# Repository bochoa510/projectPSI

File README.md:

# projectPSI : Automatic Tire Inflator prototype 

# Index

* CAD
  - housing design using OnShapeCAD
    
*  Code
   - source code used to program microcontroller
 
* Parts
    - detailed list of components used and links 
    
* Previous versions
  - previous versions, keeping for project history
    
* Resources
   - parts resources  
     
* Schematics
   - KiCAD schematic files and board design

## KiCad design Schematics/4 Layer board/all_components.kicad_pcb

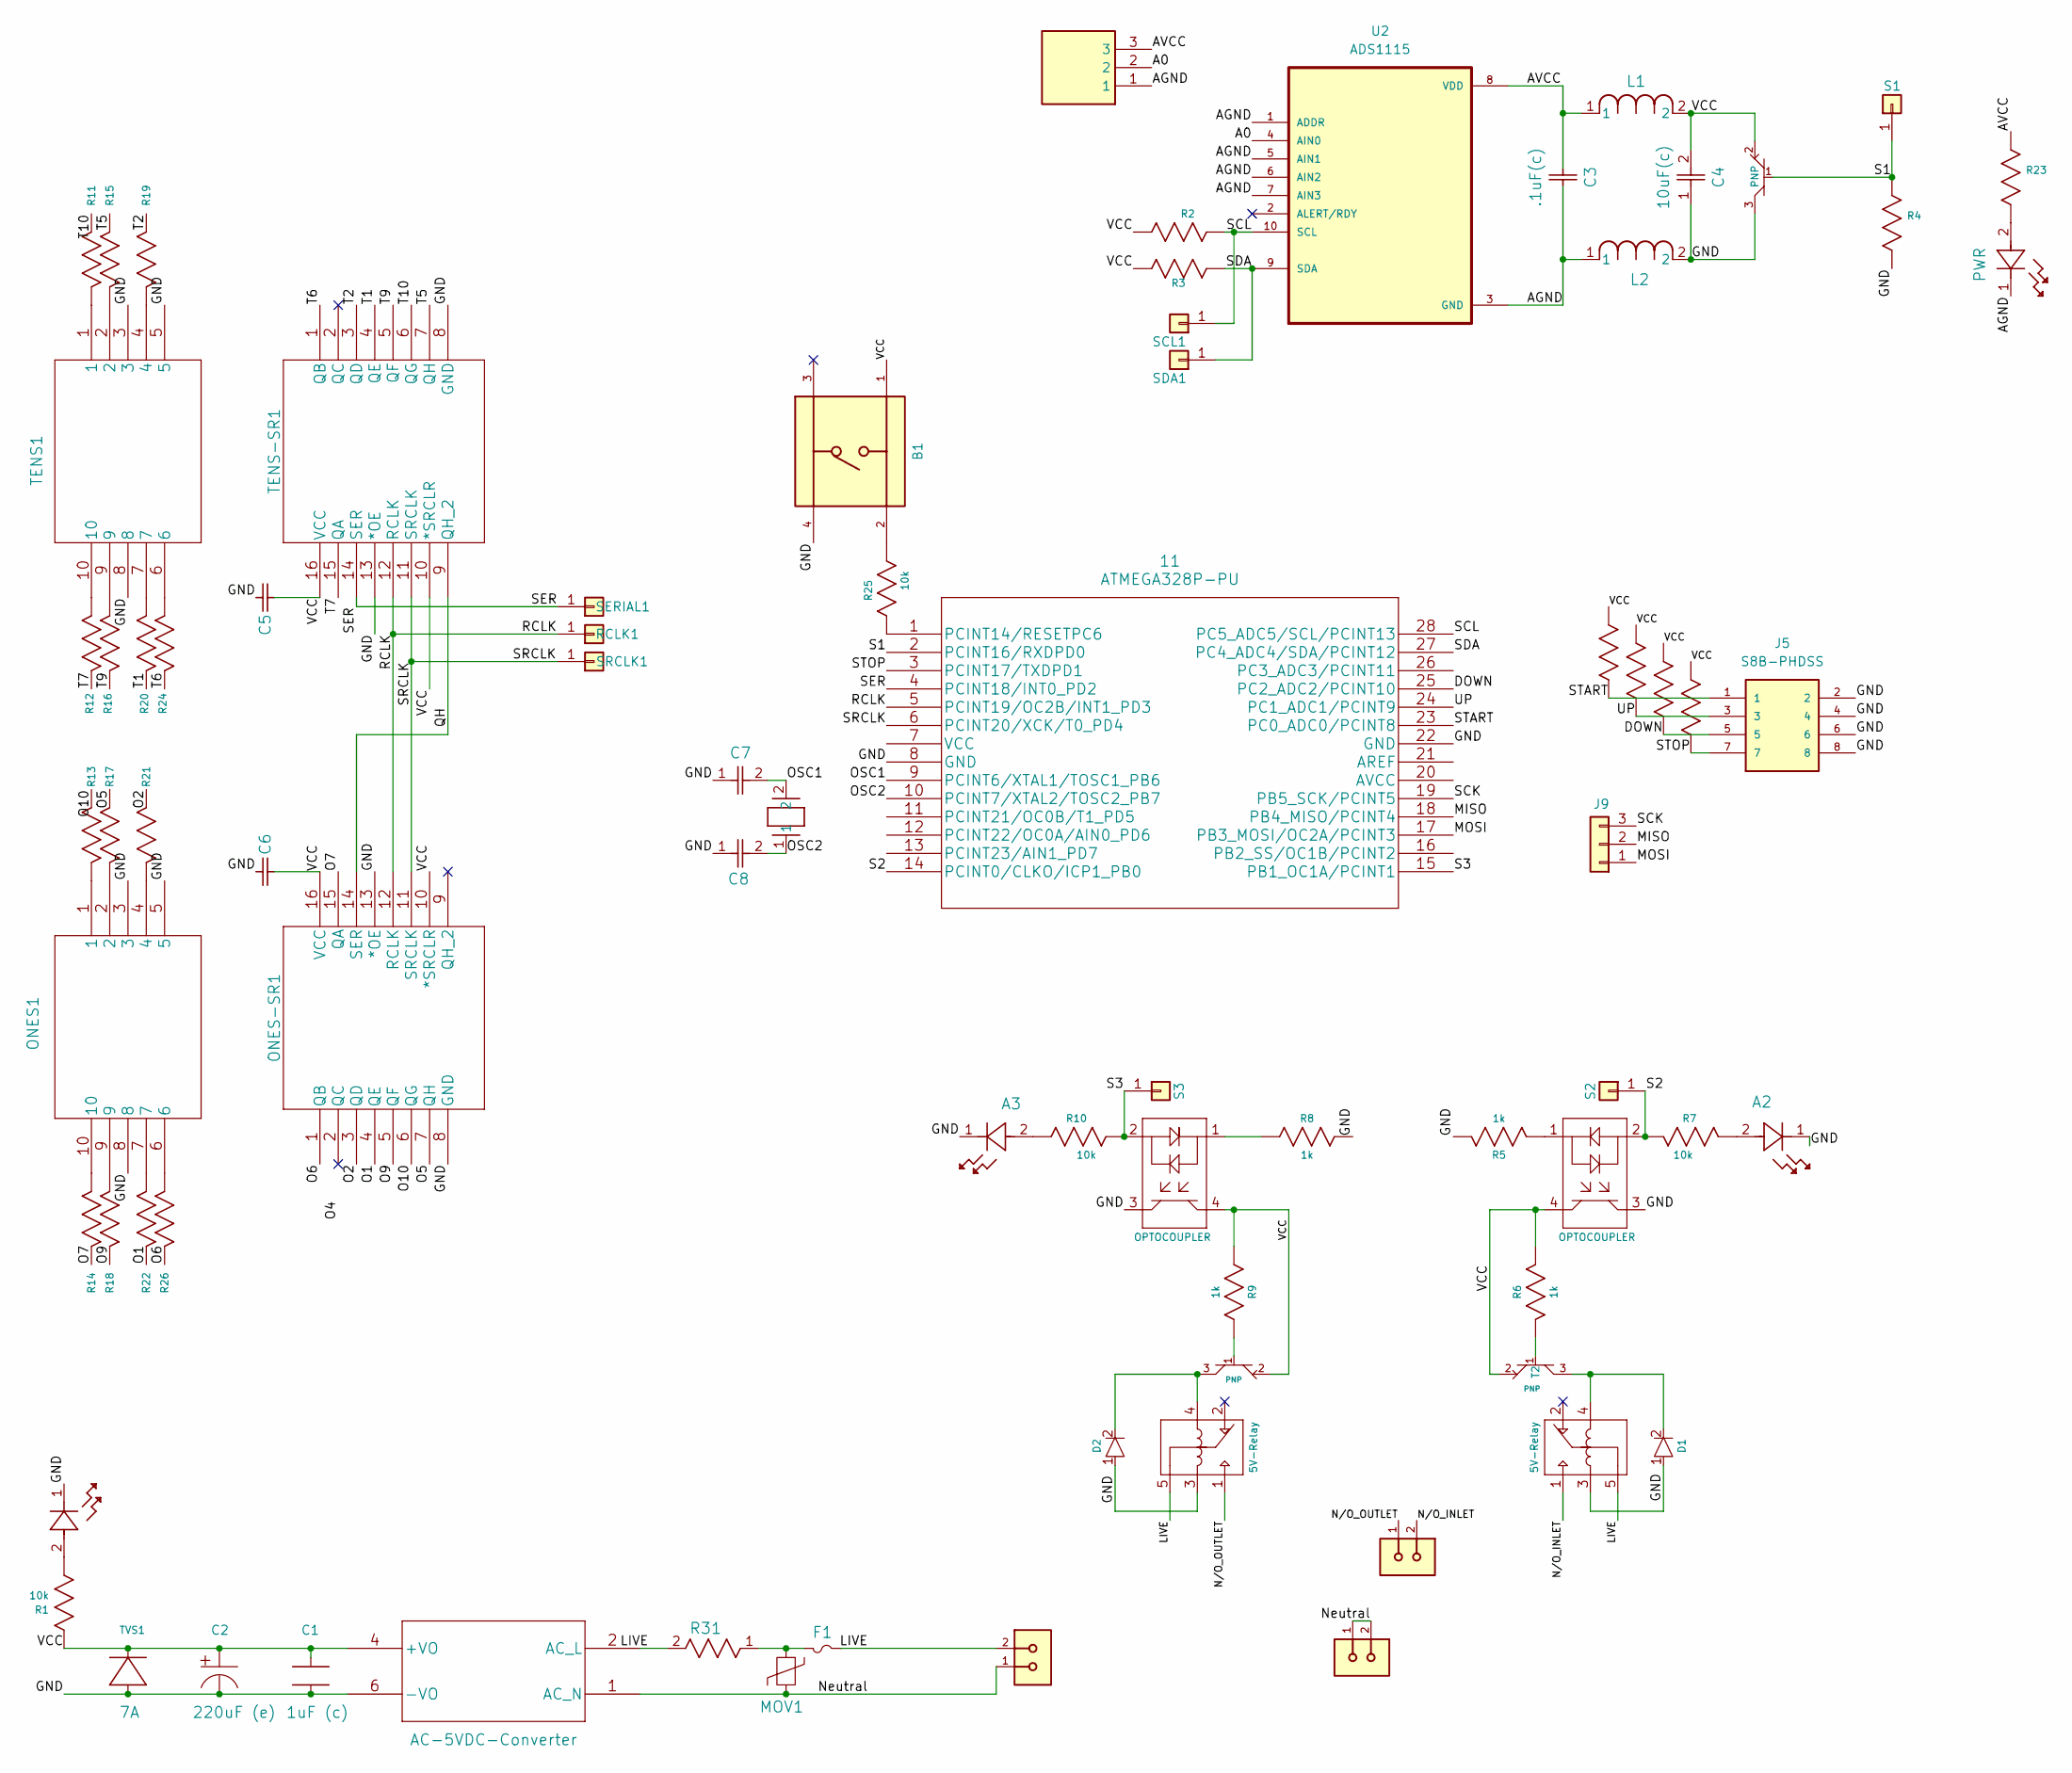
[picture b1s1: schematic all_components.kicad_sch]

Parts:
11: ATMEGA328P-PU
A2, A3: red led; red LED
B1: push button
C1: 1uF (c); 1uF(c)
C2: 220uF (e)
C3, C5, C6: .1uF(c); .1uF Cap (c)
C4: 10uF(c); 10uF Cap (c)
C7: C0805C220J5GAC7210; 22pF Cap (c)
C8: 22pF Cap (c)
D1, D2: Small-Signal-Diode; small signal diode
F1: FUSE; Fuse
J1, J2, J7: OSTTF020161; 1x2 terminal block
J3, J4: 5V-Relay; 5V Relay
J5: S8B-PHDSS; 2x4 female connector
J6: OSTVN03A150; 1x3 terminal block
J9: 3-pin-header; 3 pin header
L1, L2: Ferrite-Bead; ferrite bead
LED1, LED2: PWR; green LED
MOV1: 350V_4.5kA MOV
ONES1: 7-Segment-Display; 7 segment display
ONES-SR1: 8bit-Shift-Register; 8 bit shift register
Q1, Q2: OPTOCOUPLER; optocoupler
R1, R4, R7, R10, R23, R25: 10k; 10kohm
R2, R3: 10kohm
R5, R6, R8, R9, R27, R28, R29, R30: 1k; 1kohm
R11, R12, R13, R14, R15, R16, R17, R18, R19, R20, R21, R22, R24, R26: 100ohm-Resistor; 100ohm
R31: 6.8ohm
RCLK1: Conn_01x01; 1 pin header
S1, S2, S3: Conn_01x01; 1 pin header
SCL1: Conn_01x01; 1 pin header
SDA1: Conn_01x01; 1 pin header
SERIAL1: Conn_01x01; 1 pin header
SRCLK1: Conn_01x01; 1 pin header
T1, T2, T3: PNP; PNP Transistor
TENS1: 7-Segment-Display; 7 segment display
TENS-SR1: 8bit-Shift-Register; 8 bit shift register
TVS1: 7A; 7A TVS diode
U2: ADS1115
XTAL1: HCM4916000000ABJT; Oscillator
u3: AC-5VDC-Converter; CONV_PSK-10D-5

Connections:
/A0: J6.2, U2.4 (AIN0)
/AGND: C3.1, J6.1, L2.1, LED2.1, U2.1 (ADDR), U2.3 (GND), U2.5 (AIN1), U2.6 (AIN2), U2.7 (AIN3)
/AVCC: C3.2, J6.3, L1.1, R23.2, U2.8 (VDD)
/DOWN: 11.25 (PC2_ADC2/PCINT10), J5.5, R29.2
/GND: 11.8 (GND), 11.22 (GND), A2.1, A3.1, B1.4, C1.2, C2.2, C4.1, C5.2, C6.2, C7.1, C8.1, D1.1, D2.1, J3.3, J4.3, J5.2, J5.4, J5.6, J5.8, L2.2, LED1.1, ONES1.3, ONES1.5, ONES1.8, ONES-SR1.8 (GND), ONES-SR1.13 (*OE), Q1.3, Q2.3, R4.1, R5.1, R8.2, T1.3, TENS1.3, TENS1.5, TENS1.8, TENS-SR1.8 (GND), TENS-SR1.13 (*OE), TVS1.2, u3.6 (-VO)
/LIVE: F1.2, J1.2, J3.5, J4.5, R31.2, u3.2 (AC_L)
/MISO: 11.18 (PB4_MISO/PCINT4), J9.2
/MOSI: 11.17 (PB3_MOSI/OC2A/PCINT3), J9.1
/Neutral: J1.1, J2.1, J2.2, MOV1.1, u3.1 (AC_N)
/N/O_INLET: J3.1, J7.2
/N/O_OUTLET: J4.1, J7.1
/O1: ONES-SR1.4 (QE), R22.2
/O2: ONES-SR1.3 (QD), R21.1
/O5: ONES-SR1.7 (QH), R17.1
/O6: ONES-SR1.1 (QB), R26.2
/O7: ONES-SR1.15 (QA), R14.2
/O9: ONES-SR1.5 (QF), R18.2
/O10: ONES-SR1.6 (QG), R13.1
/OSC1: 11.9 (PCINT6/XTAL1/TOSC1_PB6), C7.2, XTAL1.2
/OSC2: 11.10 (PCINT7/XTAL2/TOSC2_PB7), C8.2, XTAL1.1
/QH: ONES-SR1.14 (SER), TENS-SR1.9 (QH_2)
/RCLK: 11.5 (PCINT19/OC2B/INT1_PD3), ONES-SR1.12 (RCLK), RCLK1.1, TENS-SR1.12 (RCLK)
/S1: 11.2 (PCINT16/RXDPD0), R4.2, S1.1, T1.1
/S2: 11.14 (PCINT0/CLKO/ICP1_PB0), Q1.2, R7.2, S2.1
/S3: 11.15 (PB1_OC1A/PCINT1), Q2.2, R10.2, S3.1
/SCK: 11.19 (PB5_SCK/PCINT5), J9.3
/SCL: 11.28 (PC5_ADC5/SCL/PCINT13), R2.2, SCL1.1, U2.10 (SCL)
/SDA: 11.27 (PC4_ADC4/SDA/PCINT12), R3.2, SDA1.1, U2.9 (SDA)
/SER: 11.4 (PCINT18/INT0_PD2), SERIAL1.1, TENS-SR1.14 (SER)
/SRCLK: 11.6 (PCINT20/XCK/T0_PD4), ONES-SR1.11 (SRCLK), SRCLK1.1, TENS-SR1.11 (SRCLK)
/START: 11.23 (PC0_ADC0/PCINT8), J5.1, R27.2
/STOP: 11.3 (PCINT17/TXDPD1), J5.7, R30.2
/T1: R20.2, TENS-SR1.4 (QE)
/T2: R19.1, TENS-SR1.3 (QD)
/T5: R15.1, TENS-SR1.7 (QH)
/T6: R24.2, TENS-SR1.1 (QB)
/T7: R12.2, TENS-SR1.15 (QA)
/T9: R16.2, TENS-SR1.5 (QF)
/T10: R11.1, TENS-SR1.6 (QG)
/UP: 11.24 (PC1_ADC1/PCINT9), J5.3, R28.2
/VCC: B1.1, C1.1, C2.1, C4.2, C5.1, C6.1, L1.2, ONES-SR1.10 (*SRCLR), ONES-SR1.16 (VCC), Q1.4, Q2.4, R1.2, R2.1, R3.1, R6.1, R9.1, R27.1, R28.1, R29.1, R30.1, T1.2, T2.2, T3.2, TENS-SR1.10 (*SRCLR), TENS-SR1.16 (VCC), TVS1.1, u3.4 (+VO)
unnamed: 11.1 (PCINT14/RESETPC6), R25.1
unnamed: A2.2, R7.1
unnamed: A3.2, R10.1
unnamed: B1.2, R25.2
unnamed: D1.2, J3.4, T2.3
unnamed: D2.2, J4.4, T3.3
unnamed: F1.1, MOV1.2, R31.1
unnamed: LED1.2, R1.1
unnamed: LED2.2, R23.1
unnamed: ONES1.1, R13.2
unnamed: ONES1.2, R17.2
unnamed: ONES1.4, R21.2
unnamed: ONES1.6, R26.1
unnamed: ONES1.7, R22.1
unnamed: ONES1.9, R18.1
unnamed: ONES1.10, R14.1
unnamed: Q1.1, R5.2
unnamed: Q2.1, R8.1
unnamed: R6.2, T2.1
unnamed: R9.2, T3.1
unnamed: R11.2, TENS1.1
unnamed: R12.1, TENS1.10
unnamed: R15.2, TENS1.2
unnamed: R16.1, TENS1.9
unnamed: R19.2, TENS1.4
unnamed: R20.1, TENS1.7
unnamed: R24.1, TENS1.6

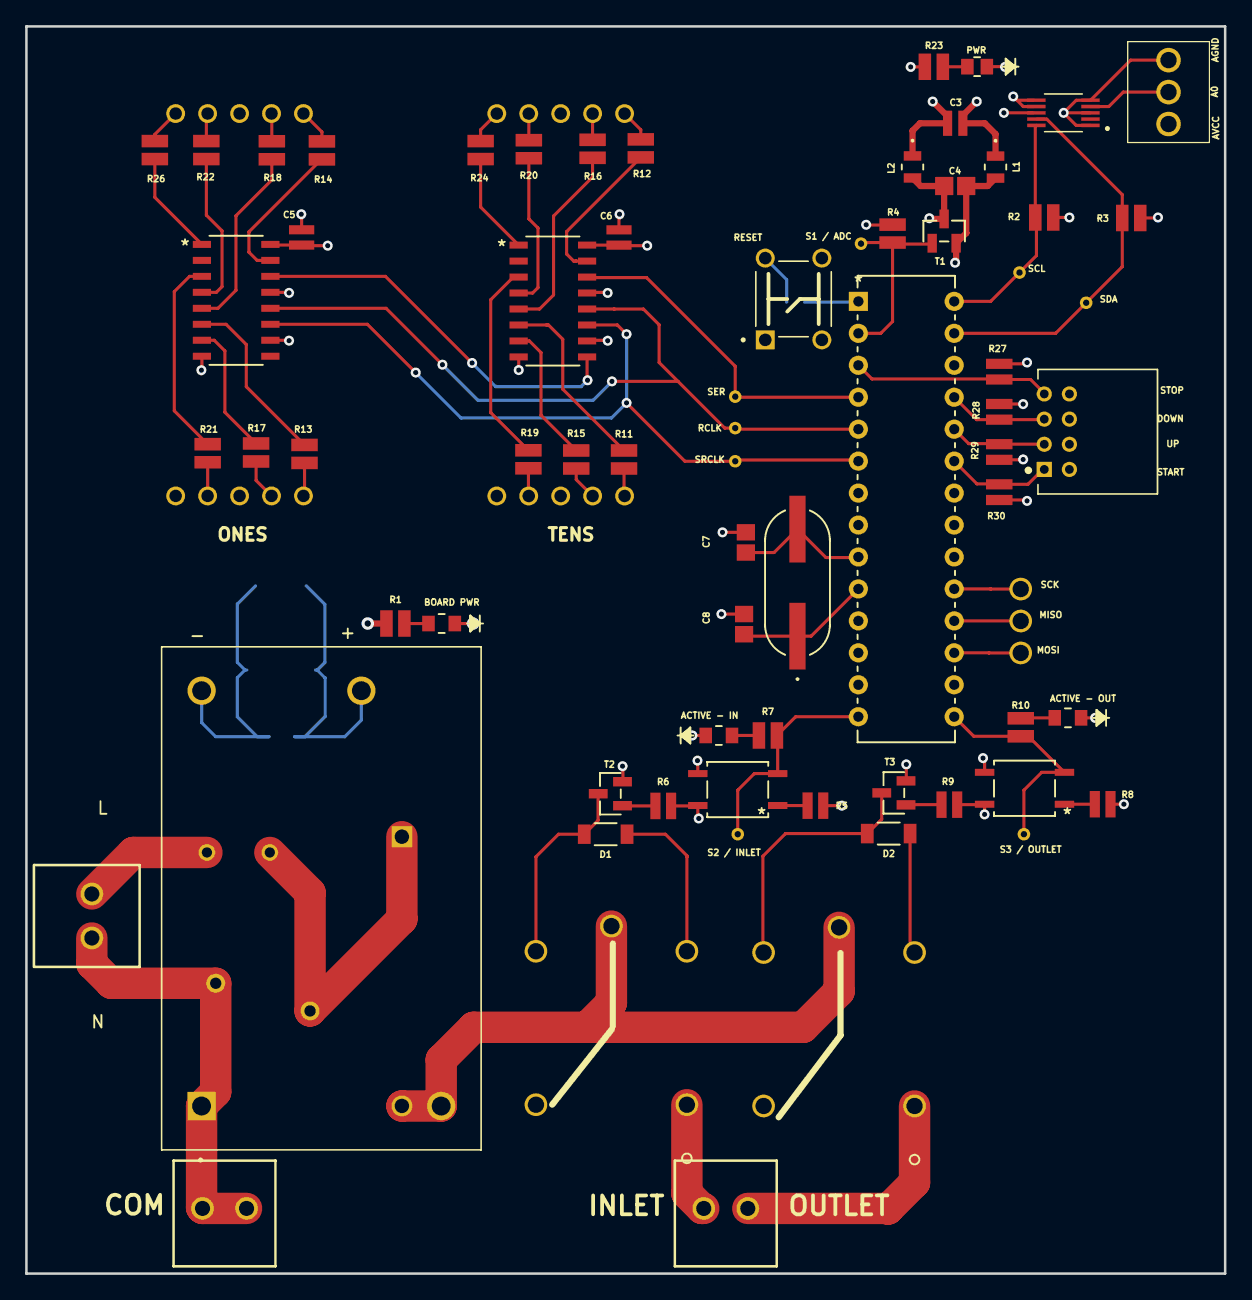
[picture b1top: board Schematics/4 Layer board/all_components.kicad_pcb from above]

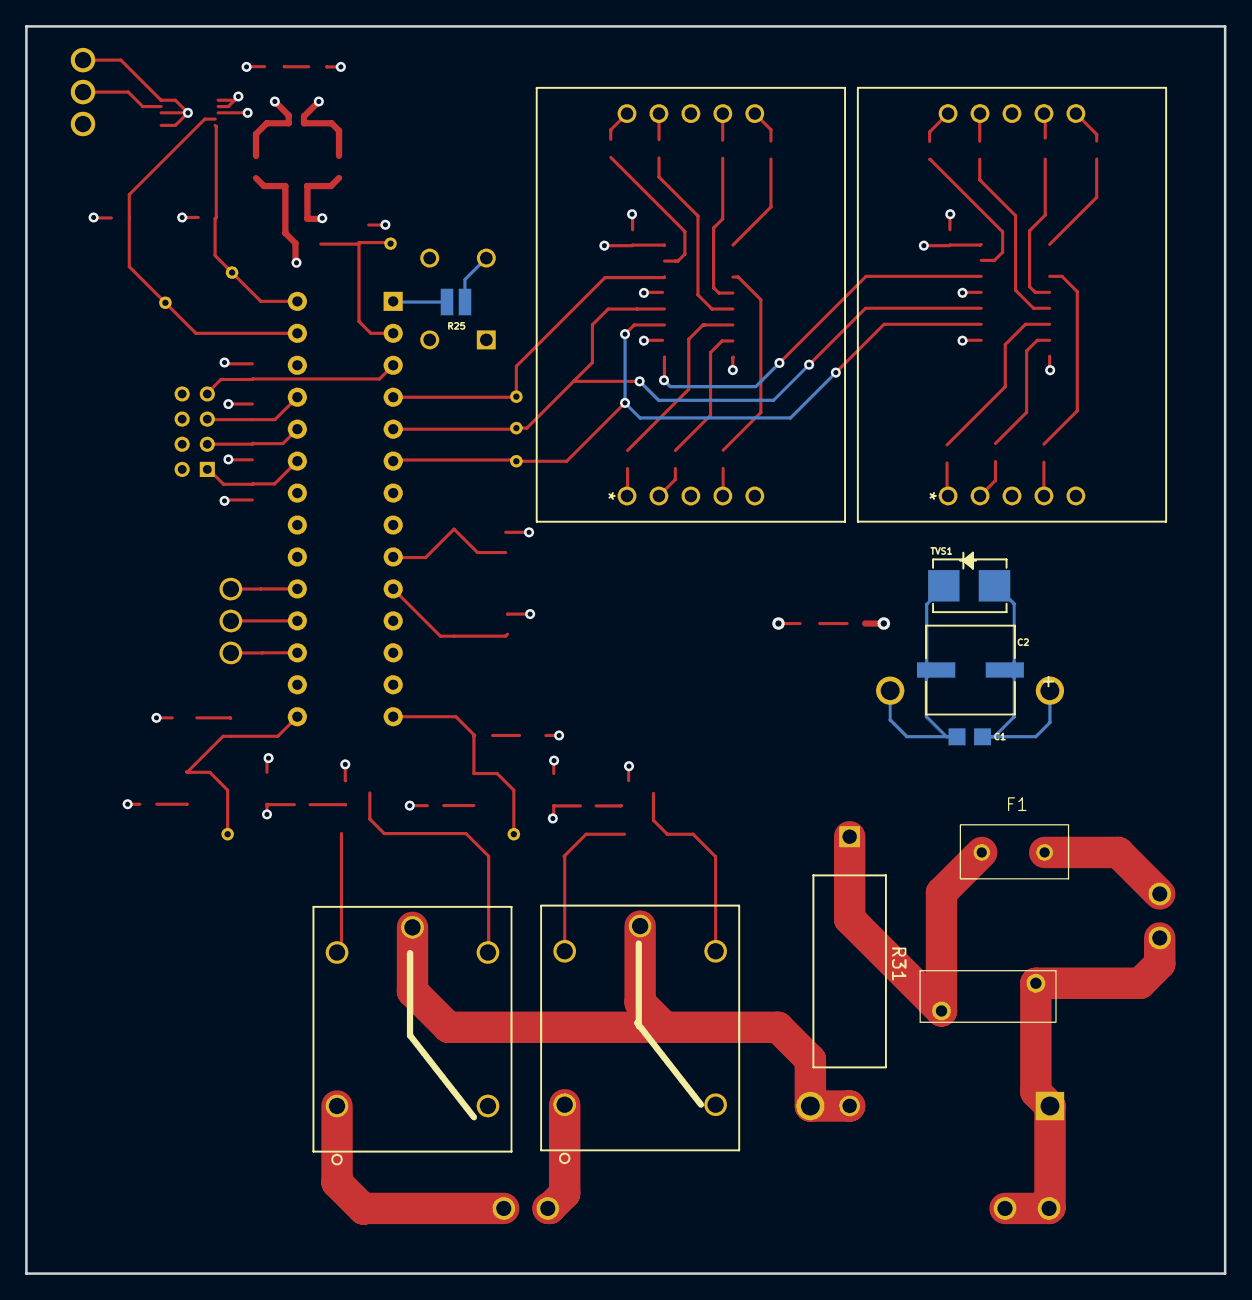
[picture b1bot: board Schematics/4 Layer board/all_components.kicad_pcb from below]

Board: 4 copper layers, 95.3 x 99.2 mm, 80 parts (11 on the bottom side), 68 nets.

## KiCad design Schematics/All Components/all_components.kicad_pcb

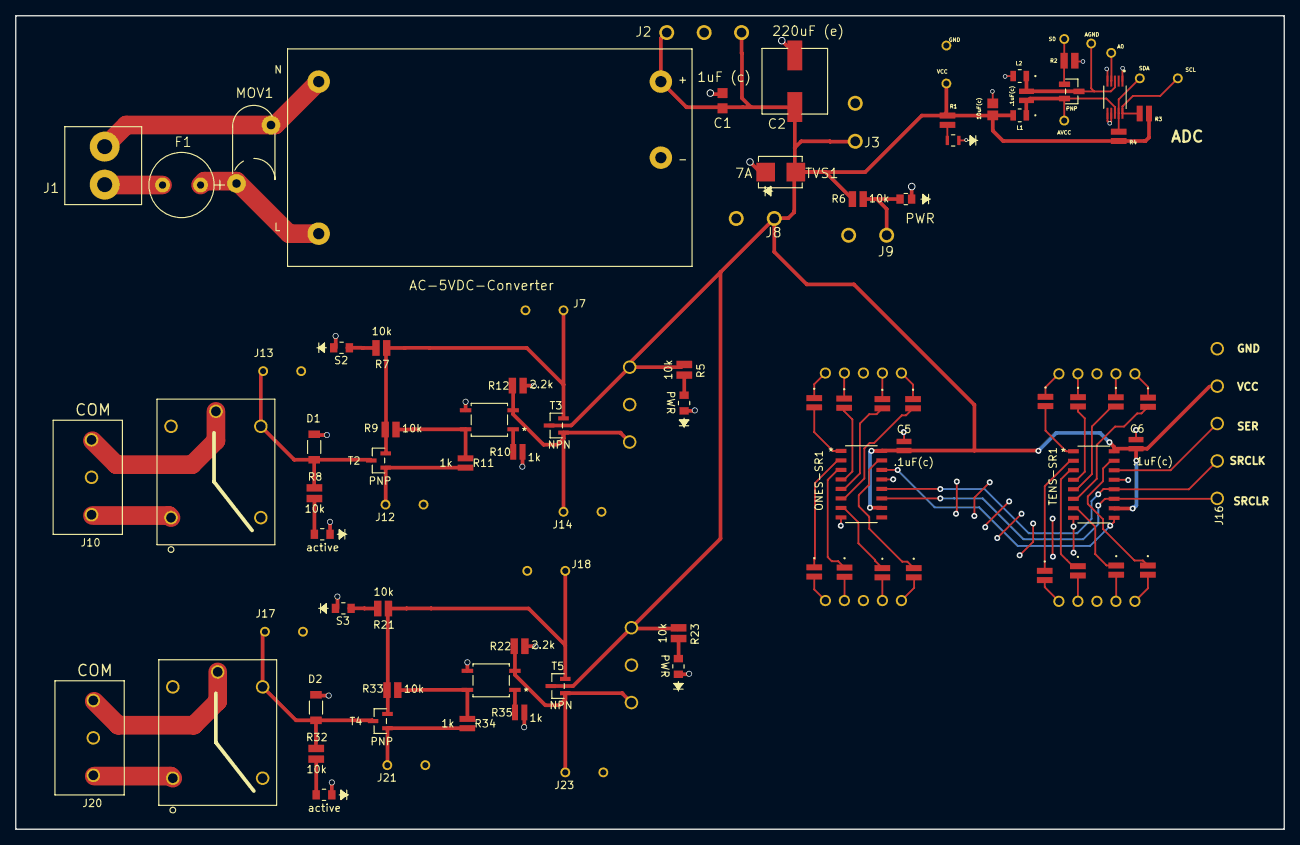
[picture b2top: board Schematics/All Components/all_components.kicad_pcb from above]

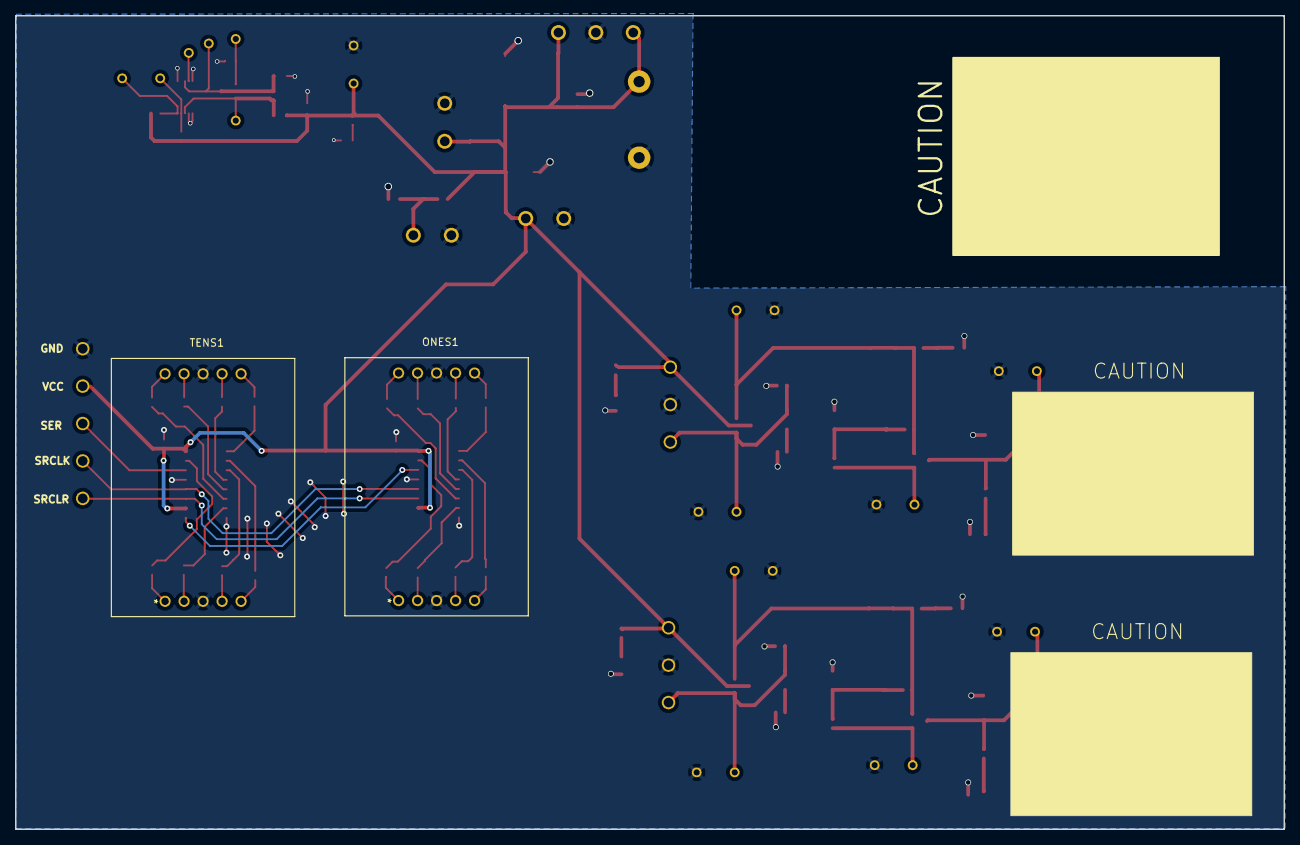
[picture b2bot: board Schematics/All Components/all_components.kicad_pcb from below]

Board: 4 copper layers, 169.5 x 108.7 mm, 95 parts (2 on the bottom side), 62 nets.

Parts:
AGND: Conn_01x01; 1 pin header
AVCC: Conn_01x01; 1 pin header
C1: 1uF (c); 1uF ceramic capacitor
C2: 220uF (e); 220uF electrolytic capacitor
C3, C5, C6: .1uF(c); .1uF ceramic capacitor
C4: 10uF(c); 10uF Ceramic Capacitor
D1, D2: Small-Signal-Diode; small signal diode
F1: FUSE
J1: 2-pin-terminal-block
J2: Conn_01x03; 3 pin header
J3, J7, J8, J9, J12, J13, J14, J17, J18, J21, J23: Conn_01x02; 2 pin header
J4, J5: 2-pin-header; 2 pin header
J6: Conn_01x01; 1 pin header
J10, J20: 3-pin-terminal-block
J11, J22: 5V-Relay; 5V Relay
J15: S1; 3 pin header
J16: 5-pin-header; 5 pin header
J19: S2; 3 pin header
L1, L2: Ferrite-Bead; ferrite bead
LED1, LED2: PWR; green LED
MOV1: 470V-Varistor; 470V Varistor
ONES1: 7-Segment-Display; 7 segment display
ONES-SR1: 8bit-Shift-Register; 8 bit shift register
PWR: green led; green LED
PWR#2: green led; green LED
Q1, Q2: OPTOCOUPLER; optocoupler
R1, R2, R5, R6, R7, R8, R9, R21, R23, R32, R33: 10k; 10kohm resistor
R3, R4: 10kohm; 10kohm resistor
R10, R11, R34, R35: 1k; 1kohm resistor
R12, R22: 2.2k; 2.2kohm resisitor
R13, R14, R15, R16, R17, R18, R19, R20, R24, R25, R26, R27, R28, R29, R30, R31: 100ohm-Resistor; 100ohm resistor
S0: Conn_01x01; 1 pin header
S2, S3: green led; green LED
T1, T2, T4: PNP; PNP Transistor
T3, T5: NPN; NPN Transistor
TENS1: 7-Segment-Display; 7 segment display
TENS-SR1: 8bit-Shift-Register; 8 bit shift register
TVS1: 7A; 7A TVS diode
U1: ADS1115IDGST; ADS1115
active: red led; red LED
active#2: red led; red LED
u1: AC-5VDC-Converter; ac-dc converter

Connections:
/A0: J6.1, U1.4 (AIN0)
/AGND: AGND.1, C3.1, L2.1, T1.3, U1.3 (GND)
/AVCC: AVCC.1, C3.2, L1.1, T1.2, U1.8 (VDD)
/COM_INLET: J10.1, J11.5, J20.1, J22.5
/GND: C1.1, C2.2, C4.1, C5.2, C6.2, D1.1, D2.1, J2.2, J3.2, J4.2, J7.2, J8.2, J9.2, J10.2, J11.3, J12.2, J13.2, J14.2, J15.2, J16.5, J17.2, J18.2, J19.2, J20.2, J21.2, J22.3, J23.2, L2.2, LED1.1, LED2.1, ONES1.3, ONES1.8, ONES-SR1.8 (GND), ONES-SR1.13 (*OE), PWR.1, PWR#2.1, Q1.3, Q2.1, Q2.3, R2.1, R10.2, R12.1, R22.1, R35.1, R35.2, S2.1, S3.1, TENS1.3, TENS1.8, TENS-SR1.8 (GND), TENS-SR1.13 (*OE), TVS1.2, U1.1 (ADDR), U1.5 (AIN1), U1.6 (AIN2), U1.7 (AIN3), active.1, active#2.1, u1.3 (-VO)
/INLET_VCC: J7.1, R7.2, R9.2, T2.2, T3.2
/LIVE: F1.2, J1.1
/Neutral: J1.2, MOV1.1, u1.1 (AC_N)
/N/O_INLET: J10.3, J11.1, J20.3, J22.1
/O1: ONES-SR1.4 (QE), R16.2
/O2: ONES-SR1.3 (QD), R26.1
/O4: ONES-SR1.2 (QC), R24.1
/O5: ONES-SR1.7 (QH), R27.1
/O6: ONES-SR1.1 (QB), R13.2
/O7: ONES-SR1.15 (QA), R25.1
/O9: ONES-SR1.5 (QF), R15.2
/O10: ONES-SR1.6 (QG), R14.2
/OUTLET_VCC: J18.1, R21.1, R21.2, R33.2, S3.2, T4.2, T5.2
/QH: ONES-SR1.14 (SER), TENS-SR1.9 (QH_2)
/RCLK: J16.2, ONES-SR1.12 (RCLK), TENS-SR1.12 (RCLK)
/S0: R2.2, S0.1, T1.1
/S1: J14.1, J15.3, Q1.2, R12.2, T3.1
/S2: J19.3, J23.1, Q2.2, R22.2, T5.1
/SCL: J5.2, R3.2, U1.10 (SCL)
/SDA: J5.1, R4.2, U1.9 (SDA)
/SER: J16.3, TENS-SR1.14 (SER)
/SRCLK: J16.1, ONES-SR1.11 (SRCLK), TENS-SR1.11 (SRCLK)
/T1: R17.2, TENS-SR1.4 (QE)
/T2: R31.1, TENS-SR1.3 (QD)
/T4: R29.1, TENS-SR1.2 (QC)
/T5: R30.1, TENS-SR1.7 (QH)
/T6: R19.2, TENS-SR1.1 (QB)
/T7: R28.1, TENS-SR1.15 (QA)
/T9: R18.2, TENS-SR1.5 (QF)
/T10: R20.2, TENS-SR1.6 (QG)
/VCC: C1.2, C2.1, C4.2, C5.1, C6.1, J2.1, J2.3, J3.1, J4.1, J8.1, J15.1, J16.4, J19.1, L1.2, ONES-SR1.10 (*SRCLR), ONES-SR1.16 (VCC), PWR.2, PWR#2.2, R1.2, R3.1, R4.1, R5.1, R5.2, R6.2, R23.1, R23.2, T3.3, T5.3, TENS-SR1.10 (*SRCLR), TENS-SR1.16 (VCC), TVS1.1, u1.4 (+VO)
J12: J12.1, Q1.4, R9.1, R11.1, R11.2, T2.1
J17: D2.2, J17.1, J22.4, R32.1, T4.3
J21: J21.1, Q2.4, R33.1, R34.1, R34.2, T4.1
unnamed: J9.1, LED2.2, R6.1
unnamed: D1.2, J11.4, J13.1, R8.1, R8.2, T2.3, active#2.2
unnamed: LED1.2, R1.1
unnamed: ONES1.1, R25.2
unnamed: ONES1.2, R27.2
unnamed: ONES1.4, R26.2
unnamed: ONES1.5, R24.2
unnamed: ONES1.6, R13.1
unnamed: ONES1.7, R16.1
unnamed: ONES1.9, R15.1
unnamed: ONES1.10, R14.1
unnamed: Q1.1, R10.1
unnamed: R7.1, S2.2
unnamed: R28.2, TENS1.1
unnamed: R30.2, TENS1.2
unnamed: R31.2, TENS1.4
unnamed: R29.2, TENS1.5
unnamed: R20.1, TENS1.10
unnamed: R18.1, TENS1.9
unnamed: R17.1, TENS1.7
unnamed: R19.1, TENS1.6
unnamed: F1.1, MOV1.2, u1.2 (AC_L)
OUT_PWR: R32.2, active.2

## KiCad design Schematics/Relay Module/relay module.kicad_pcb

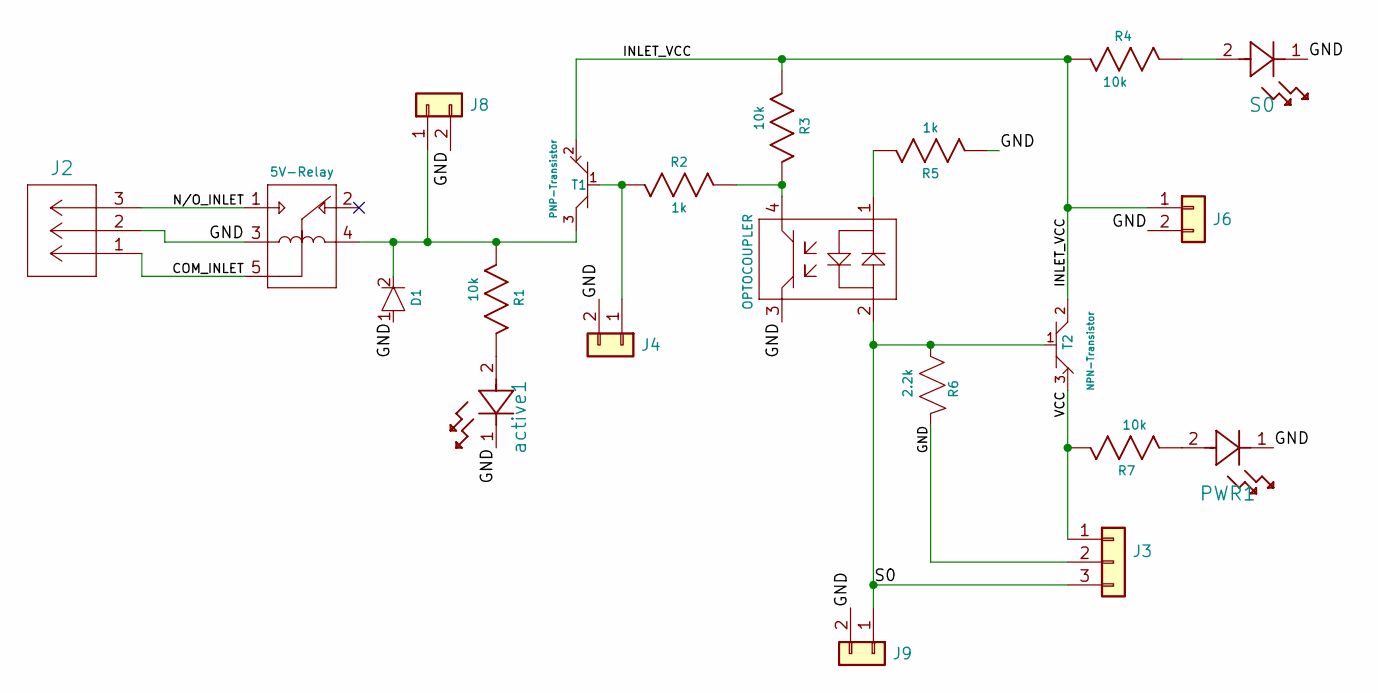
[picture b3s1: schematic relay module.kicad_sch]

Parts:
D1: Small-Signal-Diode; small signal diode
J1: 5V-Relay; 5V Relay
J2: 3-pin-terminal-block
J3: Conn_01x03; 3 pin header
J4, J6, J8, J9: Conn_01x02; 2 pin header
PWR1: green led; green LED
Q1: OPTOCOUPLER; optocoupler
R1, R3, R4, R7: 10k; 10kohm resistor
R2, R5: 1k; 1kohm resistor
R6: 2.2k; 2.2kohm resisitor
S0: green led; green LED
T1: PNP-Transistor; PNP Transistor
T2: NPN-Transistor; NPN Transistor
active1: red led; red LED

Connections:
/COM_INLET: J1.5, J2.1
/GND: D1.1, J1.3, J2.2, J3.2, J4.2, J6.2, J8.2, J9.2, Q1.3, R5.2, R6.1, S0.1; also elsewhere on the board
/INLET_VCC: J6.1, R3.2, R4.2, T1.2, T2.2
/N/O_INLET: J1.1, J2.3
/S0: J3.3, J9.1, Q1.2, R6.2, T2.1
/VCC: J3.1, R7.1, T2.3
unnamed: J4.1, R2.2, T1.1
unnamed: D1.2, J1.4, J8.1, R1.2, T1.3
unnamed 8: R7.2; also elsewhere on the board
unnamed: Q1.1, R5.1
unnamed: Q1.4, R2.1, R3.1
unnamed 11: R1.1; also elsewhere on the board
unnamed: R4.1, S0.2

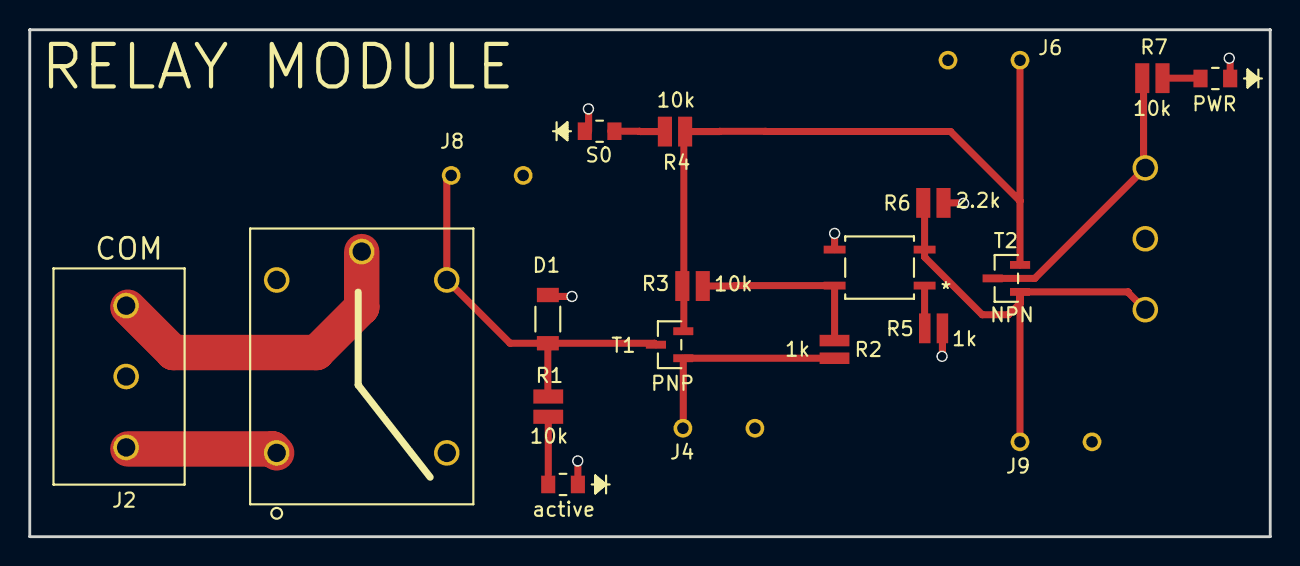
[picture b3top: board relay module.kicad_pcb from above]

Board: 2 copper layers, 87.5 x 35.8 mm, 21 parts (0 on the bottom side), 13 nets.

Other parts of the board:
PWR: green led; green LED
active: red led; red LED

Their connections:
/GND: PWR.1, active.1; also elsewhere on the board
unnamed 8: PWR.2; also elsewhere on the board
unnamed 11: active.2; also elsewhere on the board

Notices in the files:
parts and their libraries:
Copyright 2016 Accelerated Designs. All rights reserved.
